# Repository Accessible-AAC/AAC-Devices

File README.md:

# AAC-Devices

Augmentative and alternative communications device design files based on inexpensive and open source technologies.

Printed circuit boards were designed using KiCAD (https://www.kicad.org/)

Enclosures were designed using OpenSCAD version 2015.03-2 (https://www.openscad.org/).

Solutions are designed around commodity electronic devices that should be inexpensive and readily available on-line.

<br />
This work is licensed under a <a rel="license" href="http://creativecommons.org/licenses/by-sa/4.0/">
Creative Commons Attribution-ShareAlike 4.0 International License</a>.

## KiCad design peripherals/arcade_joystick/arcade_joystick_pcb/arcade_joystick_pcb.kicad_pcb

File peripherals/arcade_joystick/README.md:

# Arcade Joystick

These directories contain design files for an arcade joystick peripheral.
 
This sensor can be plugged into an analog (yellow) controller input. It is activated by moving the handle.

## Assembly

Internal hardware mechanism is an arcade style 4/8 way joystick purchased from China.

It is held in place by four 8-32 x 1½" machine screws inserted into 4 embedded 8-32 nuts.

The joystick is connected to the interface PCB using hook-up wire:

    80 mm twisted pair soldered to D+, D-
    80 mm twisted pair soldered to R+, R-
    130 mm twisted pair soldered to L+, L-
    130 mm twisted pair soldered to U+, U-

## Handles

The threads on the joystick handle are compatible with an M6 nut.

<br />This work is licensed under a <a rel="license" href="http://creativecommons.org/licenses/by-sa/4.0/">
Creative Commons Attribution-ShareAlike 4.0 International License</a>.

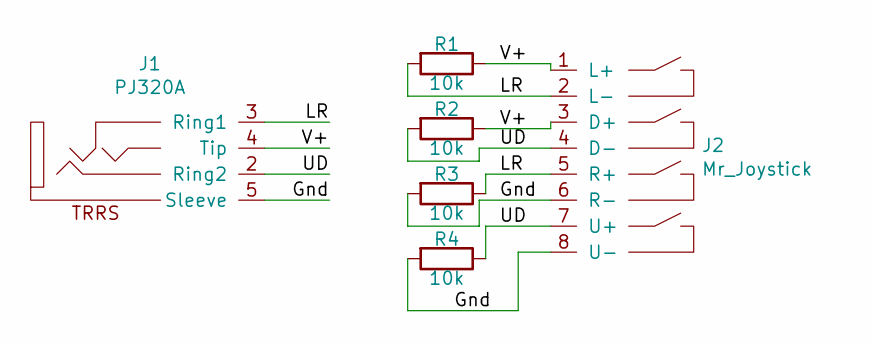
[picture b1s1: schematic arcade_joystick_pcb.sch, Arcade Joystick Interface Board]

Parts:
J1: PJ320A; PJ-320A
J2: Mr_Joystick
R1, R2, R3, R4: 10k; R_1206_3216Metric; LCSC C17902

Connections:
/Gnd: J1.5 (Sleeve), J2.6 (R-), J2.8 (U-), R3.2, R4.2
/LR: J1.3 (Ring1), J2.2 (L-), J2.5 (R+), R1.2, R3.1
/UD: J1.2 (Ring2), J2.4 (D-), J2.7 (U+), R2.2, R4.1
/V+: J1.4 (Tip), J2.1 (L+), J2.3 (D+), R1.1, R2.1

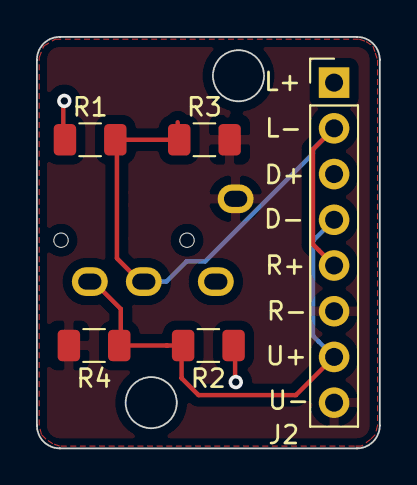
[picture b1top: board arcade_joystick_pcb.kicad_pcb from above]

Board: 2 copper layers, 19.1 x 22.9 mm, 6 parts (1 on the bottom side), 4 nets.

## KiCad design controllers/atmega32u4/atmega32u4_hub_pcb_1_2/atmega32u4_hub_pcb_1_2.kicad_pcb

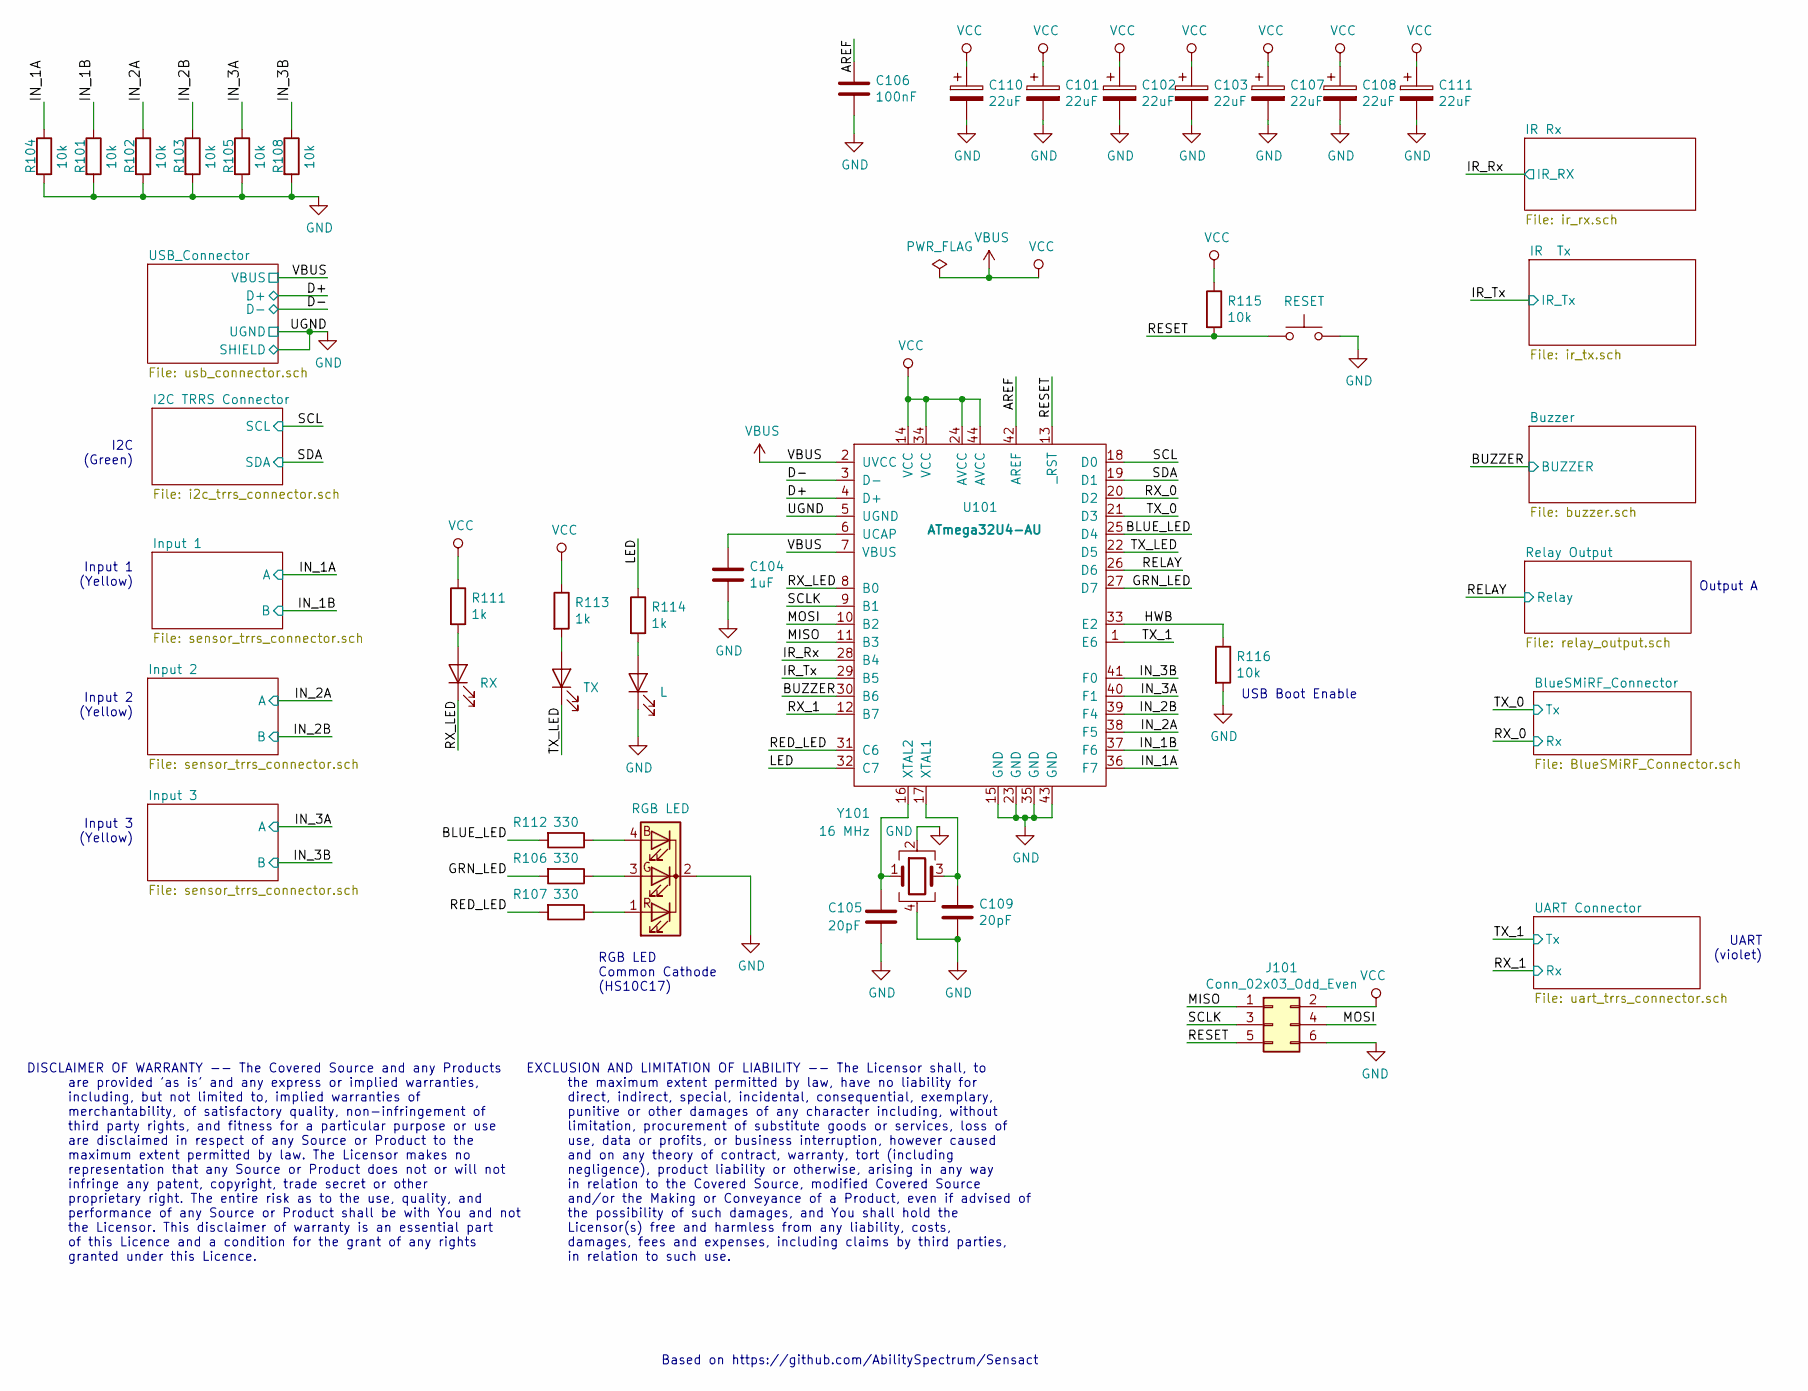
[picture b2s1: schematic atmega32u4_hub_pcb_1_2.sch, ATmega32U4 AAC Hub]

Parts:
C101, C102, C103, C107, C108, C110, C111: 22uF; C_0805_2012Metric; LCSC C45783
C104: 1uF; C_0805_2012Metric; LCSC C28323
C105, C109: 20pF; C_0603_1608Metric; LCSC C1648
C106: 100nF; C_0805_2012Metric; LCSC C49678
D101: RX; LED_0603_1608Metric; LCSC C72043
D102: RGB LED; LED_D5.0mm-4_RGB
D103: TX; LED_0603_1608Metric; LCSC C2286
D104: L; LED_0603_1608Metric; LCSC C72038
J101: Conn_02x03_Odd_Even; PinHeader_2x03_P2.54mm_Vertical
R101, R102, R103, R104, R105, R108, R115, R116: 10k; R_0603_1608Metric; LCSC C25804
R106, R107, R112: 330; R_0603_1608Metric; LCSC C23138
R111, R113, R114: 1k; R_0603_1608Metric; LCSC C21190
SW101: RESET; SW_PUSH_6mm
U101: ATmega32U4-AU; TQFP-44_10x10mm_P0.8mm; LCSC C44854
Y101: 16 MHz; Crystal_SMD_3225-4Pin_3.2x2.5mm; LCSC C13738

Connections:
/AREF: C106.1, U101.42 (AREF)
/BLUE_LED: R112.2, U101.25 (D4)
/BUZZER: U101.30 (B6); also elsewhere on the board
/D+: U101.4 (D+); also elsewhere on the board
/D-: U101.3 (D-); also elsewhere on the board
/GRN_LED: R106.2, U101.27 (D7)
/HWB: R116.1, U101.33 (E2)
/IN_3A: R105.1, U101.40 (F1); also elsewhere on the board
/IN_3B: R108.1, U101.41 (F0); also elsewhere on the board
/IR_Rx: U101.28 (B4); also elsewhere on the board
/IR_Tx: U101.29 (B5); also elsewhere on the board
/LED: R114.1, U101.32 (C7)
/MISO: J101.1, U101.11 (B3)
/MOSI: J101.4, U101.10 (B2)
/RED_LED: R107.2, U101.31 (C6)
/RELAY: U101.26 (D6); also elsewhere on the board
/RESET: J101.5, R115.2, SW101.1, U101.13 (_RST)
/RX_0: U101.20 (D2); also elsewhere on the board
/RX_1: U101.12 (B7); also elsewhere on the board
/RX_LED: D101.1 (K), U101.8 (B0)
/SCL: U101.18 (D0); also elsewhere on the board
/SCLK: J101.3, U101.9 (B1)
/SDA: U101.19 (D1); also elsewhere on the board
/TX_0: U101.21 (D3); also elsewhere on the board
/TX_1: U101.1 (E6); also elsewhere on the board
/TX_LED: D103.1 (K), U101.22 (D5)
GND: C101.2, C102.2, C103.2, C104.2, C105.2, C106.2, C107.2, C108.2, C109.2, C110.2, C111.2, D102.2 (K), D104.1 (K), J101.6, R101.2, R102.2, R103.2, R104.2, R105.2, R108.2, R116.2, SW101.2, U101.5 (UGND), U101.15 (GND), U101.23 (GND), U101.35 (GND), U101.43 (GND), Y101.2, Y101.4; also elsewhere on the board
unnamed: C104.1, U101.6 (UCAP)
unnamed: C105.1, U101.16 (XTAL2), Y101.1
unnamed: C109.1, U101.17 (XTAL1), Y101.3
unnamed: D101.2 (A), R111.2
unnamed: D102.1 (RA), R107.1
unnamed: D102.3 (GA), R106.1
unnamed: D102.4 (BA), R112.1
unnamed: D103.2 (A), R113.2
unnamed: D104.2 (A), R114.2
VBUS: C101.1, C102.1, C103.1, C107.1, C108.1, C110.1, C111.1, J101.2, R111.1, R113.1, R115.1, U101.2 (UVCC), U101.7 (VBUS), U101.14 (VCC), U101.24 (AVCC), U101.34 (VCC), U101.44 (AVCC); also elsewhere on the board

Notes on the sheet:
Input 1 (Yellow)
I2C (Green)
Input 2 (Yellow)
Input 3 (Yellow)
Output A
USB Boot Enable
RGB LED Common Cathode (HS10C17)
Based on https://github.com/AbilitySpectrum/Sensact
UART (violet)
DISCLAIMER OF WARRANTY -- The Covered Source and any Products are provided 'as is' and any express or implied warranties, including, but not limited to, implied warranties of merchantability, of satisfactory quality, non-infringement of third party rights, and fitness for a particular purpose or us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
EXCLUSION AND LIMITATION OF LIABILITY -- The Licensor shall, to the maximum extent permitted by law, have no liability for direct, indirect, special, incidental, consequential, exemplary, punitive or other damages of any character including, without limitation, procurement of substitute goods or se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

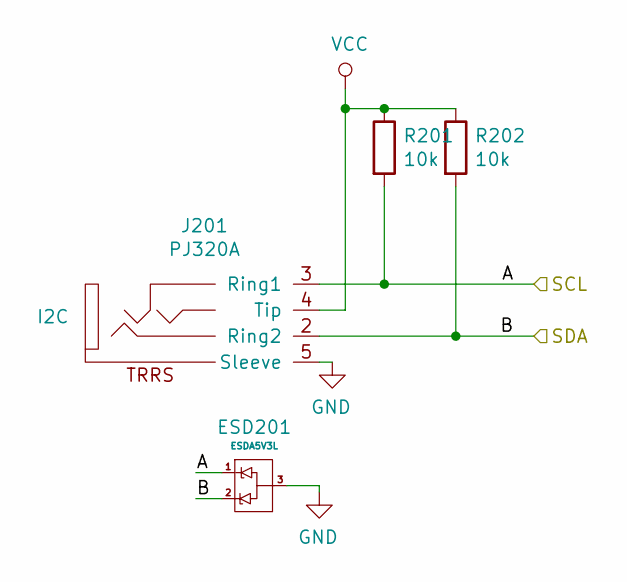
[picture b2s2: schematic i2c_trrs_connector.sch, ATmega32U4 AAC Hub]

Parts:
ESD201: ESDA5V3L; SOT-23; LCSC C87911
J201: PJ320A; PJ-320A
R201, R202: 10k; R_0603_1608Metric; LCSC C25804

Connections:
/SCL: ESD201.1, J201.3 (Ring1), R201.2; also elsewhere on the board
/SDA: ESD201.2, J201.2 (Ring2), R202.2; also elsewhere on the board
GND: ESD201.3, J201.5 (Sleeve); also elsewhere on the board
VBUS: J201.4 (Tip), R201.1, R202.1; also elsewhere on the board

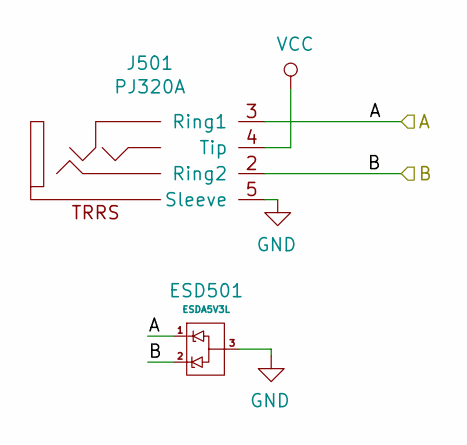
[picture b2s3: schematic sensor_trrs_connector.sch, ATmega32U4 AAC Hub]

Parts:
ESD401: ESDA5V3L; SOT-23; LCSC C87911
J301: PJ320A; PJ-320A

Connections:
GND: ESD401.3, J301.5 (Sleeve); also elsewhere on the board
VBUS: J301.4 (Tip); also elsewhere on the board

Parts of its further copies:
ESD301, ESD501: ESDA5V3L; SOT-23; LCSC C87911
J401, J501: PJ320A; PJ-320A

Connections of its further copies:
/IN_3A: ESD501.1, J501.3 (Ring1); also elsewhere on the board
/IN_3B: ESD501.2, J501.2 (Ring2); also elsewhere on the board
GND: ESD301.3, ESD501.3, J401.5 (Sleeve), J501.5 (Sleeve); also elsewhere on the board
VBUS: J401.4 (Tip), J501.4 (Tip); also elsewhere on the board

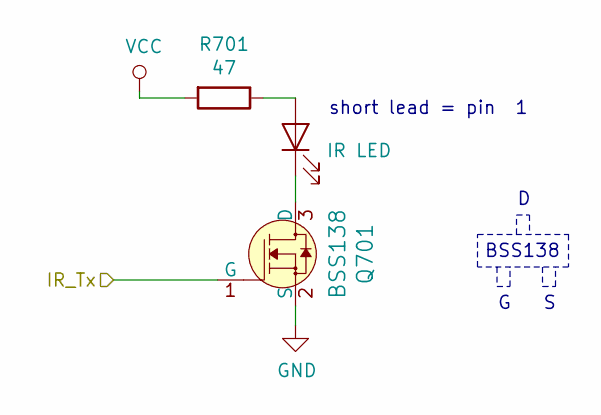
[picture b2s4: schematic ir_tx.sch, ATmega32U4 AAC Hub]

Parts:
D701: IR LED; LED_D5.0mm
Q701: BSS138; SOT-23; MPN BSS138; Digi-Key_PN BSS138CT-ND
R701: 47; R_1206_3216Metric; Part Number 1206W4J0470T5E; LCSC C25384

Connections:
/IR_Tx: Q701.1 (G); also elsewhere on the board
GND: Q701.2 (S); also elsewhere on the board
unnamed: D701.1 (K), Q701.3 (D)
unnamed: D701.2 (A), R701.1
VBUS: R701.2; also elsewhere on the board

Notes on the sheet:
BSS138
short lead = pin 1

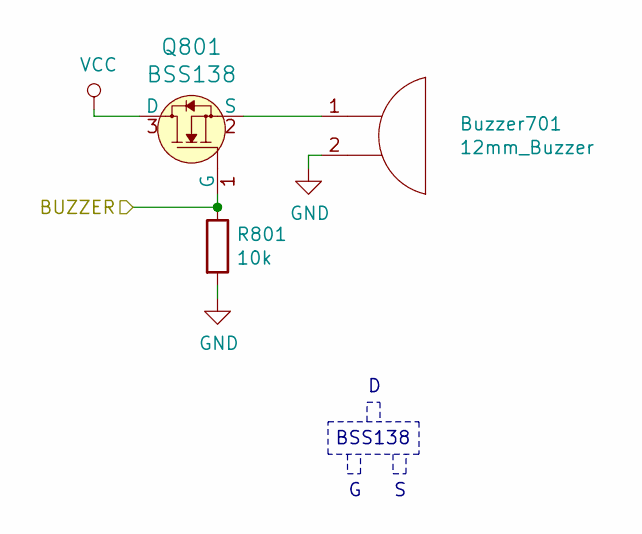
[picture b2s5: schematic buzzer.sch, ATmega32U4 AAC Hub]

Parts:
Buzzer701: 12mm_Buzzer; 12mm_buzzer
Q801: BSS138; SOT-23; MPN BSS138; Digi-Key_PN BSS138CT-ND
R801: 10k; R_0603_1608Metric; LCSC C25804

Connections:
/BUZZER: Q801.1 (G), R801.1; also elsewhere on the board
GND: Buzzer701.2, R801.2; also elsewhere on the board
unnamed: Buzzer701.1, Q801.2 (S)
VBUS: Q801.3 (D); also elsewhere on the board

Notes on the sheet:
BSS138

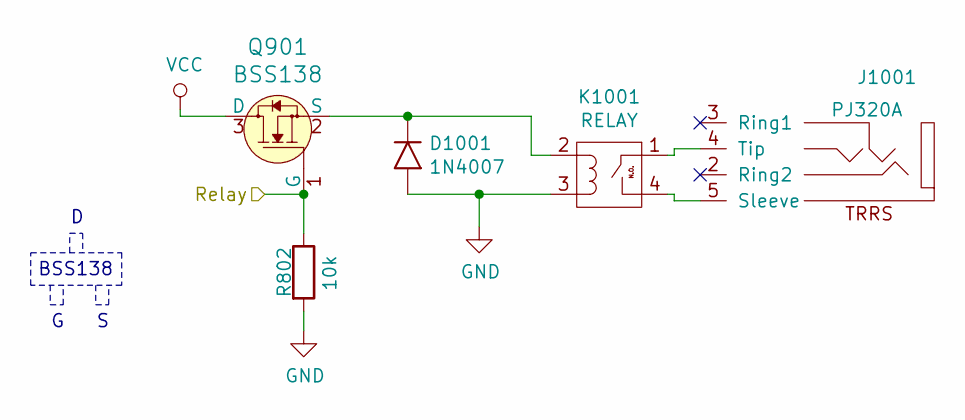
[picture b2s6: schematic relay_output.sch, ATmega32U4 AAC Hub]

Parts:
D901: 1N4007; D_SMA; LCSC C95872
J901: PJ320A; PJ-320A
K901: RELAY; sip-1a05
Q802: BSS138; SOT-23; MPN BSS138; Digi-Key_PN BSS138CT-ND
R802: 10k; R_0603_1608Metric; LCSC C25804

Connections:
/RELAY: R802.1; also elsewhere on the board
GND: R802.2; also elsewhere on the board

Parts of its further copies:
D1001: 1N4007; D_SMA; LCSC C95872
J1001: PJ320A; PJ-320A
K1001: RELAY; sip-1a05
Q901: BSS138; SOT-23; MPN BSS138; Digi-Key_PN BSS138CT-ND

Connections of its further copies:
/RELAY: Q901.1 (G); also elsewhere on the board
GND: D1001.2 (A), K1001.3; also elsewhere on the board
unnamed: D1001.1 (K), K1001.2, Q901.2 (S)
unnamed: J1001.4 (Tip), K1001.1
unnamed: J1001.5 (Sleeve), K1001.4
VBUS: Q901.3 (D); also elsewhere on the board

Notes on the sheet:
BSS138

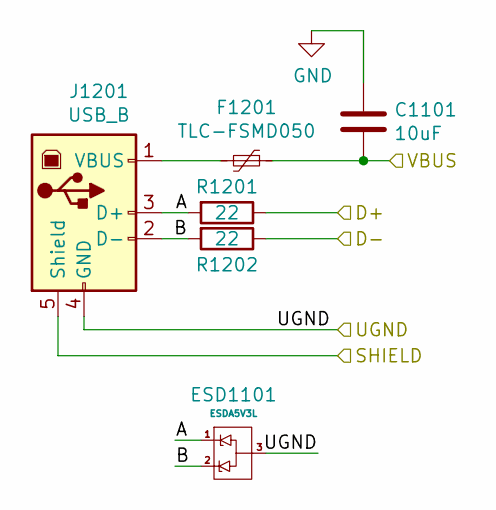
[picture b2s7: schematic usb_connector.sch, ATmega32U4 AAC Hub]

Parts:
C1101: 10uF; C_0805_2012Metric; LCSC C15850
ESD1101: ESDA5V3L; SOT-23; LCSC C87911
F1201: TLC-FSMD050; Fuse_0603_1608Metric; LCSC C261937
J1201: USB_B; USB_B_OST_USB-B1HSxx_Horizontal
R1201, R1202: 22; R_0603_1608Metric; LCSC C23345

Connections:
/D+: R1201.1; also elsewhere on the board
/D-: R1202.1; also elsewhere on the board
/USB_Connector/A: ESD1101.1, J1201.3 (D+), R1201.2
/USB_Connector/B: ESD1101.2, J1201.2 (D-), R1202.2
GND: C1101.1, ESD1101.3, J1201.4 (GND), J1201.5 (Shield); also elsewhere on the board
unnamed: F1201.2, J1201.1 (VBUS)
VBUS: C1101.2, F1201.1; also elsewhere on the board

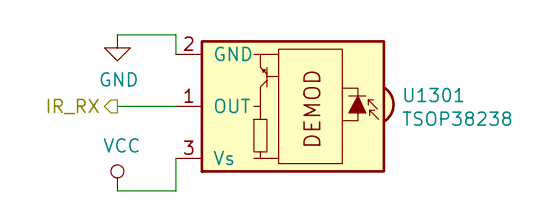
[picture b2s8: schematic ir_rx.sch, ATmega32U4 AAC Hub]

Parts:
U1301: TSOP38238; Vishay_MOLD-3Pin

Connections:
/IR_Rx: U1301.1 (OUT); also elsewhere on the board
GND: U1301.2 (GND); also elsewhere on the board
VBUS: U1301.3 (Vs); also elsewhere on the board

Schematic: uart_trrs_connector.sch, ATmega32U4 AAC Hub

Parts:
ESD1001: ESDA5V3L; SOT-23; LCSC C87911
J1101: PJ320A; PJ-320A

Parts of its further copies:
ESD1201: ESDA5V3L; SOT-23; LCSC C87911
J1202: PJ320A; PJ-320A

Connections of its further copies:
/RX_1: ESD1201.2, J1202.2 (Ring2); also elsewhere on the board
/TX_1: ESD1201.1, J1202.3 (Ring1); also elsewhere on the board
GND: ESD1201.3, J1202.5 (Sleeve); also elsewhere on the board
VBUS: J1202.4 (Tip); also elsewhere on the board

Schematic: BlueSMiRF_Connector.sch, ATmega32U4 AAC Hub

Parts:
ESD1202: ESDA5V3L; SOT-23; LCSC C87911
J1203: BlueSMiRF; BlueSMiRF_Socket

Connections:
/RX_0: ESD1202.2, J1203.3; also elsewhere on the board
/TX_0: ESD1202.1, J1203.2; also elsewhere on the board
GND: ESD1202.3, J1203.4; also elsewhere on the board
VBUS: J1203.5; also elsewhere on the board

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
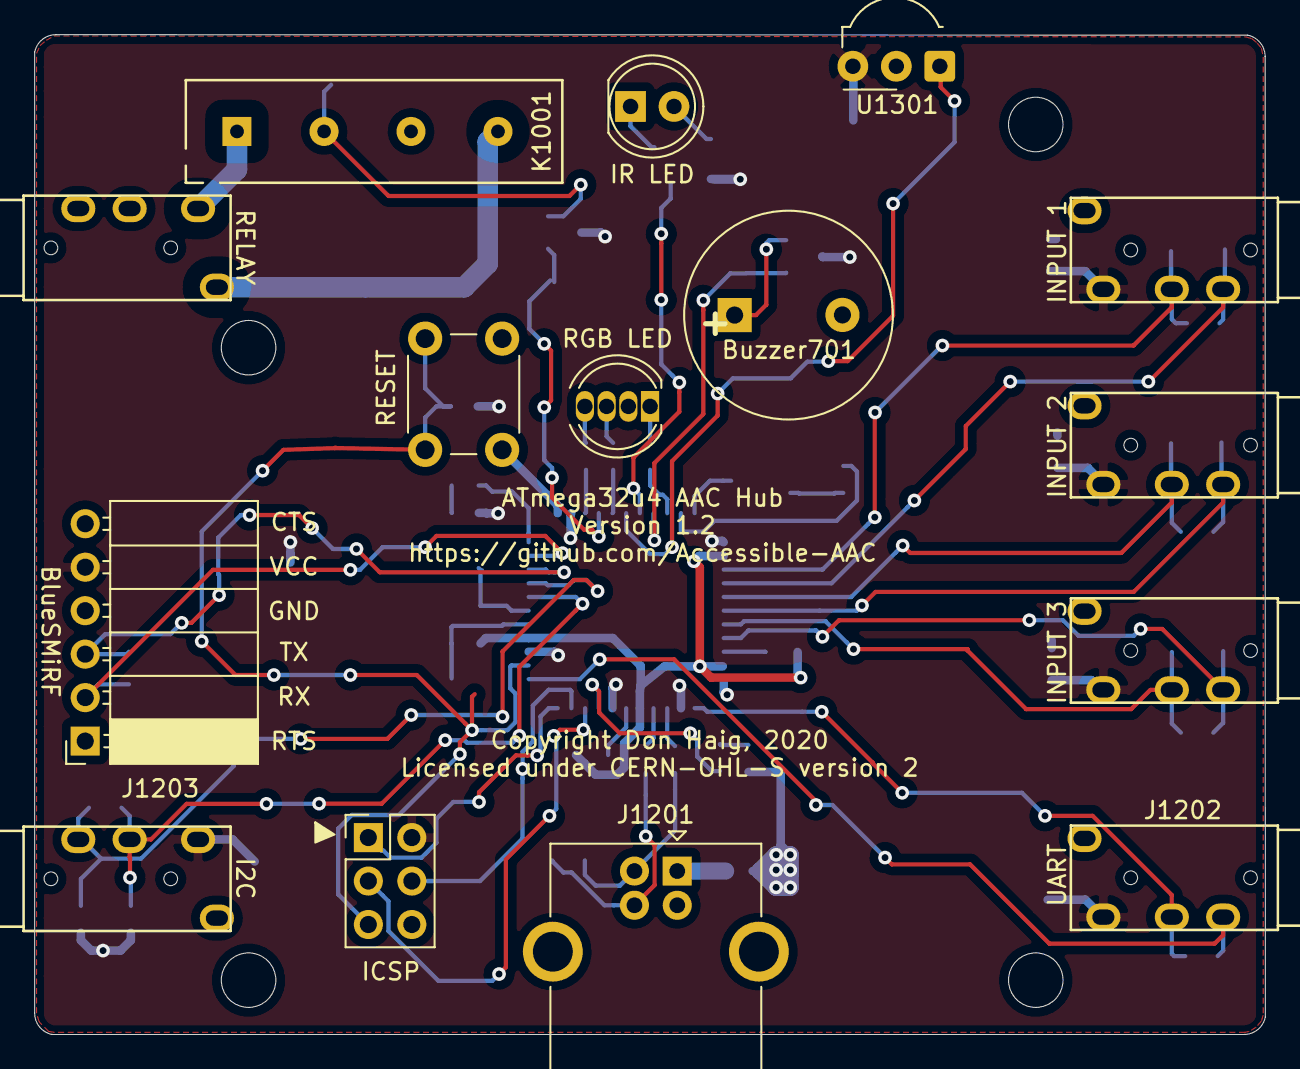
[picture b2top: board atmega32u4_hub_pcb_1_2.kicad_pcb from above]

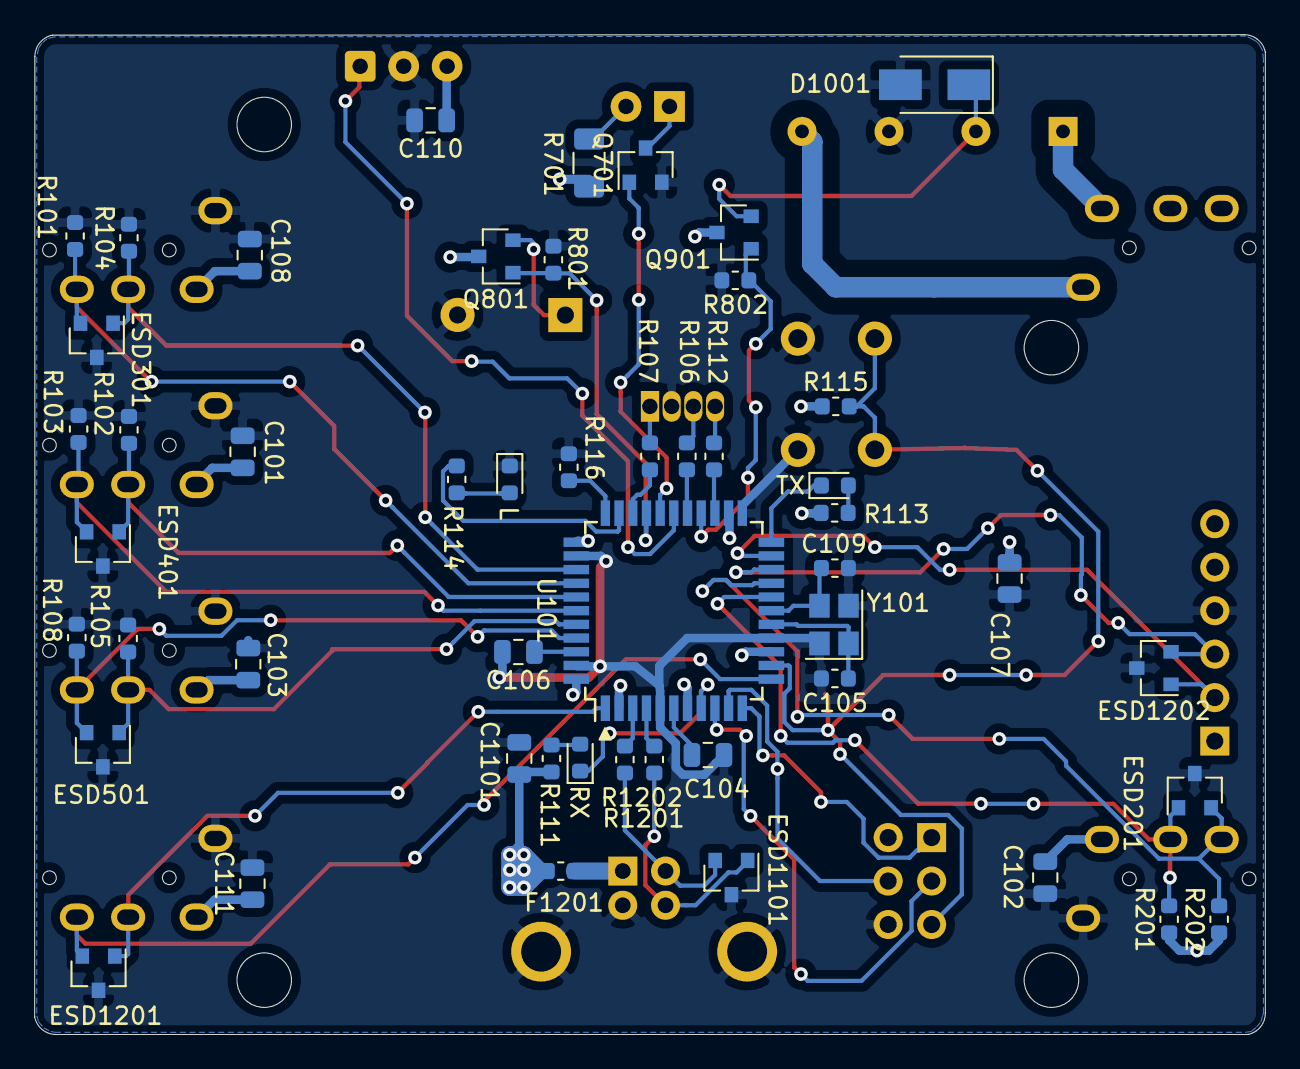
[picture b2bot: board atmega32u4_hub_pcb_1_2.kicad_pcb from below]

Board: 2 copper layers, 71.9 x 58.4 mm, 65 parts (50 on the bottom side), 50 nets.

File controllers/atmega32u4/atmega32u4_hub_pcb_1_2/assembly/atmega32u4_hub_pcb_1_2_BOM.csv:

Comment,Designator,Footprint, LCSC,
12mm_Buzzer,Buzzer701,,,https://www.aliexpress.com/item/4000133619336.html?spm=a2g0s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
22uF,"C101,C102,C103,C107,C108,C110,C111",805,C45783,https://lcsc.com/product-detail/Multilayer-Ceramic-Capacitor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
1uF,C104,805,C28323,https://lcsc.com/product-detail/Multilayer-Ceramic-Capacitor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
20pF,"C105,C109",603,C1648,https://lcsc.com/product-detail/Multilayer-Ceramic-Capacitor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
100nF,C106,805,C49678,https://lcsc.com/product-detail/Multilayer-Ceramic-Capacitor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
10uF,C1101,805,C15850,https://lcsc.com/product-detail/Multilayer-Ceramic-Capacitor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
1N4007,D1001,"SMA,DO-214AC",C95872,https://lcsc.com/product-detail/Diodes-General-Purpose_MDD-M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
RX,D101,603,C72043,https://lcsc.com/product-detail/Light-Emitting-Diodes-LED_Ev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
RGB LED,D102,,,https://www.aliexpress.com/item/1656753326.html?spm=a2g0s.90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
TX,D103,603,C72044,https://lcsc.com/product-detail/Light-Emitting-Diodes-LED_06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
L,D104,603,C72038,https://lcsc.com/product-detail/Light-Emitting-Diodes-LED_Ev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
IR LED,D701,,,
ESDA5V3L,"ESD201,ESD301,ESD401,ESD501,ESD1101,ESD1201,ESD1202",SOT-23-3, C87911,https://lcsc.com/product-detail/TVS_STMicroelectronics-ESDA5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
TLC-FSMD050,F1201,603,C261937,https://lcsc.com/product-detail/PTC-Resettable-Fuses_TLC-Ele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
Conn_02x03_Odd_Even,J101,PinHeader_2x03_P2.54mm_Vertical,C225518,https://lcsc.com/product-detail/Pin-Header-Female-Header_CJT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
USB_B,J1201,,C498173,https://lcsc.com/product-detail/New-Arrivals_SOFNG-USB-B01_C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
BlueSMiRF,J1203,, C225514,https://lcsc.com/product-detail/Pin-Header-Female-Header_CJT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
PJ320A,"J201,J301,J401,J501,J1001,J1202",,,https://www.aliexpress.com/item/32775943831.html?spm=a2g0s.9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
RELAY,K1001,,C10496,https://lcsc.com/product-detail/Relays_PAN-CHANG-SIP-1A05_C1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
BSS138,"Q701,Q801,Q901",SOT-23-3, C82045,https://lcsc.com/product-detail/MOSFET_ON-Semiconductor-BSS1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
10k,"R104,R101,R102,R103,R105,R108,R115,R116,R201,R202,R801,R802",603, C25804,https://lcsc.com/product-detail/Chip-Resistor-Surface-Mount_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
1k,"R111,R113,R114",603,C21190,https://lcsc.com/product-detail/Chip-Resistor-Surface-Mount_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
330,"R112,R106,R107",603,C23138,https://lcsc.com/product-detail/Chip-Resistor-Surface-Mount_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
22,"R1202,R1201",603,C23345,https://lcsc.com/product-detail/Chip-Resistor-Surface-Mount_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
47,R701,1206,  C25384,https://lcsc.com/product-detail/Chip-Resistor-Surface-Mount_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
RESET,SW101,6mm x 6mm, C455095,https://lcsc.com/product-detail/Tactile-Switches_XUNPU-TS-10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
ATmega32U4-AU,U101,QFP-44_10.0x10.0x0.8P,C44854,https://lcsc.com/product-detail/ATMEL-AVR_ATMEL_ATMEGA32U4-A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
TSOP38238,U1301,,,
16 MHz,Y101,SMD-3225_4P, C13738,https://lcsc.com/product-detail/SMD-Crystal-Resonators_Yangx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

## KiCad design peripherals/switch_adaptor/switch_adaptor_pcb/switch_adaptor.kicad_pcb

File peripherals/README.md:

# AAC Peripherals

These directories contain design files for various AAC peripherals.

The bases of the peripherals are colour coded according to the controller input that they should be plugged into:

Yellow : Analog (yellow) inputs

Green : I2C (green) inputs

<br />This work is licensed under a <a rel="license" href="http://creativecommons.org/licenses/by-sa/4.0/">
Creative Commons Attribution-ShareAlike 4.0 International License</a>.

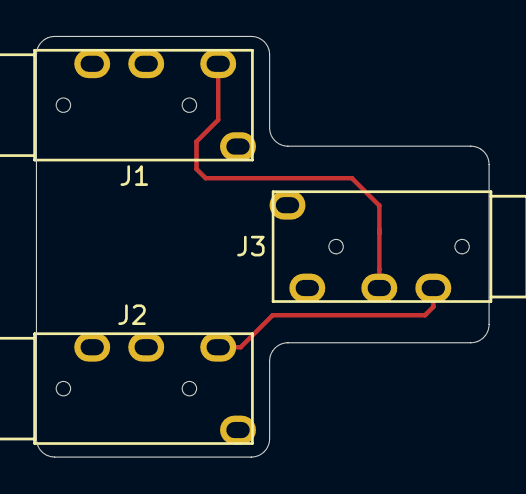
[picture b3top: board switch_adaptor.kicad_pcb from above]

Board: 2 copper layers, 25.1 x 23.4 mm, 3 parts (0 on the bottom side), 3 nets.

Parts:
J1, J2, J3: PJ320A; PJ-320A

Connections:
/SW1: J1.4, J3.3
/SW2: J2.4, J3.2
/Vcc: J1.2, J1.3, J1.5, J2.2, J2.3, J2.5, J3.4

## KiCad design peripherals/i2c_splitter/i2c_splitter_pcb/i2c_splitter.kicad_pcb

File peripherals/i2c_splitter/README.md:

# I2C Splitter

These directories contain design files for an i2c bus splitter, for use with an i2c (green) controller input.

This splitter can be used to connect two i2c (green base) peripherals to the same i2c (green) input port.

(Multiple splitters can be daisy-chained together to accommodate more i2c peripherals, subject to i2c bus limitation
with respect to peripheral addressing.)

## Assembly                                                                                                                                       

<br />This work is licensed under a <a rel="license" href="http://creativecommons.org/licenses/by-sa/4.0/">
Creative Commons Attribution-ShareAlike 4.0 International License</a>.

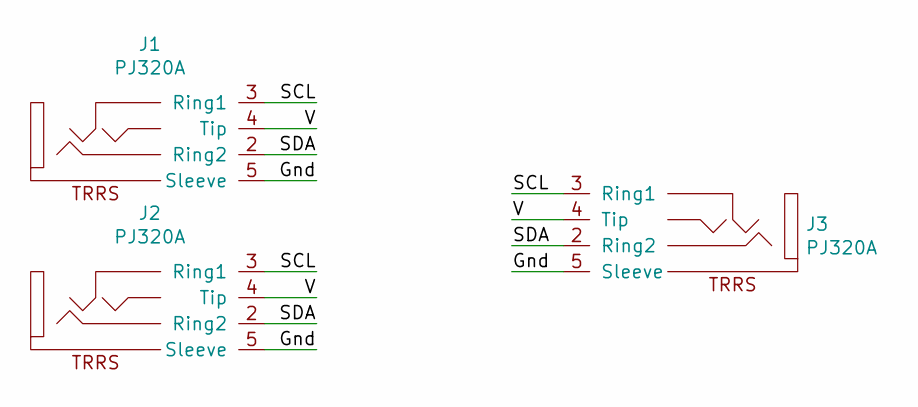
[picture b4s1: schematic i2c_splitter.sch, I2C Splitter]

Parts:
J1, J2, J3: PJ320A; PJ-320A

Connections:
/Gnd: J1.5 (Sleeve), J2.5 (Sleeve), J3.5 (Sleeve)
/SCL: J1.3 (Ring1), J2.3 (Ring1), J3.3 (Ring1)
/SDA: J1.2 (Ring2), J2.2 (Ring2), J3.2 (Ring2)
/V: J1.4 (Tip), J2.4 (Tip), J3.4 (Tip)

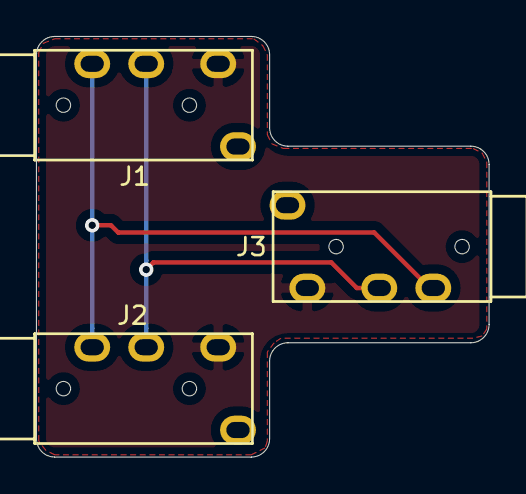
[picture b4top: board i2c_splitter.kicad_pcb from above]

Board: 2 copper layers, 25.1 x 23.4 mm, 3 parts (0 on the bottom side), 4 nets.

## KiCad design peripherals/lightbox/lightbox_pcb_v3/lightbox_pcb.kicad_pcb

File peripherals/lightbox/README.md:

# Lightbox Display

These directories contain design files for a lightbox display peripheral, for use with an i2c (green) controller input.

## Hardware

The lightbox is based on a Microchip MCP23008 8-Bit I/O Expander: <a rel="datasheet" 
href="https://ww1.microchip.com/downloads/en/DeviceDoc/21919e.pdf">Datasheet</a>

I2C Address: 0x20

## Assembly

<br />This work is licensed under a <a rel="license" href="http://creativecommons.org/licenses/by-sa/4.0/">
Creative Commons Attribution-ShareAlike 4.0 International License</a>.

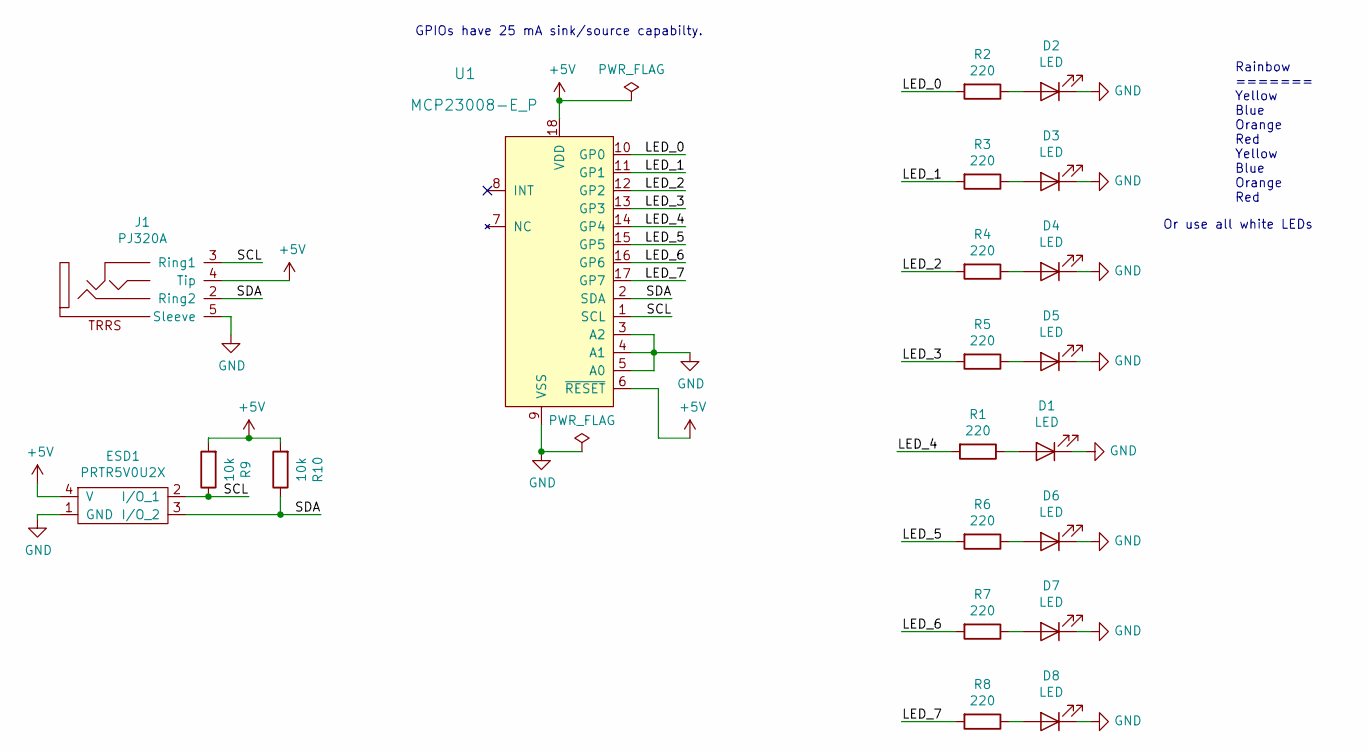
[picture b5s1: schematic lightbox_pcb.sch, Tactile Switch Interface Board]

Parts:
D1, D2, D3, D4, D5, D6, D7, D8: LED; LED_D3.0mm
ESD1: PRTR5V0U2X; SOT-143
J1: PJ320A; PJ-320A
R1, R2, R3, R4, R5, R6, R7, R8: 220; R_Axial_DIN0207_L6.3mm_D2.5mm_P7.62mm_Horizontal
R9, R10: 10k; R_Axial_DIN0207_L6.3mm_D2.5mm_P7.62mm_Horizontal
U1: MCP23008-E_P; DIP-18_W7.62mm; MPN MCP23008-E/P; Digi-Key_PN MCP23008-E/P-ND

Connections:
+5V: ESD1.4 (V), J1.4 (Tip), R9.2, R10.2, U1.6 (~RESET), U1.18 (VDD)
/LED_0: R2.2, U1.10 (GP0)
/LED_1: R3.2, U1.11 (GP1)
/LED_2: R4.2, U1.12 (GP2)
/LED_3: R5.2, U1.13 (GP3)
/LED_4: R1.2, U1.14 (GP4)
/LED_5: R6.2, U1.15 (GP5)
/LED_6: R7.2, U1.16 (GP6)
/LED_7: R8.2, U1.17 (GP7)
/SCL: ESD1.2 (I/O_1), J1.3 (Ring1), R9.1, U1.1 (SCL)
/SDA: ESD1.3 (I/O_2), J1.2 (Ring2), R10.1, U1.2 (SDA)
GND: D1.1 (K), D2.1 (K), D3.1 (K), D4.1 (K), D5.1 (K), D6.1 (K), D7.1 (K), D8.1 (K), ESD1.1 (GND), J1.5 (Sleeve), U1.3 (A2), U1.4 (A1), U1.5 (A0), U1.9 (VSS)
unnamed: D1.2 (A), R1.1
unnamed: D2.2 (A), R2.1
unnamed: D3.2 (A), R3.1
unnamed: D4.2 (A), R4.1
unnamed: D5.2 (A), R5.1
unnamed: D6.2 (A), R6.1
unnamed: D7.2 (A), R7.1
unnamed: D8.2 (A), R8.1

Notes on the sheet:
GPIOs have 25 mA sink/source capabilty.
Rainbow ======= Yellow Blue Orange Red Yellow Blue Orange Red
Or use all white LEDs

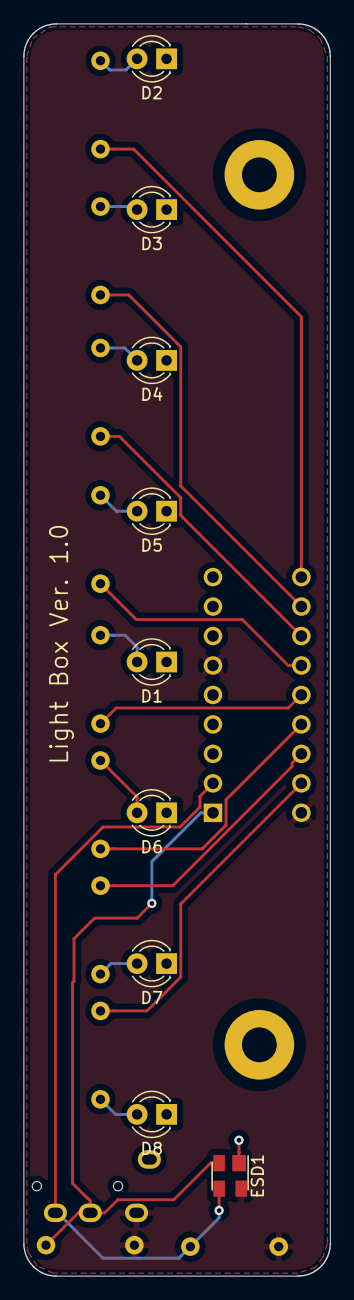
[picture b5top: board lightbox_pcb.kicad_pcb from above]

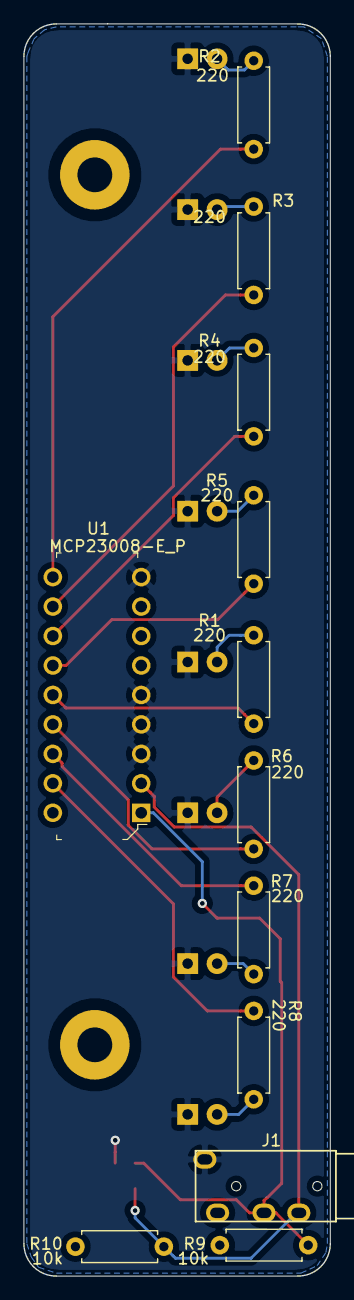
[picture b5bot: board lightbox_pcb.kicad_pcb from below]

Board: 2 copper layers, 26.4 x 108.0 mm, 23 parts (12 on the bottom side), 20 nets.

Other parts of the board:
1pin_prototyping, 1pin_prototyping#2: val**; 1pin_prototyping

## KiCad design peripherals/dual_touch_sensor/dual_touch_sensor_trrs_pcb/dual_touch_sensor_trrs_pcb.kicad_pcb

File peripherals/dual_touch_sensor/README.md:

# Dual Catalex Touch Sensor

These directories contain design files for a dual catalex touch sensor peripheral.

This sensor can be plugged into an analog (yellow) controller input. It is activated by touching the top, where indicated.

## Assembly

Catalex touch sensors should be tested before assembly to ensure that they will function correctly through the enclosure.

<br />This work is licensed under a <a rel="license" href="http://creativecommons.org/licenses/by-sa/4.0/">
Creative Commons Attribution-ShareAlike 4.0 International License</a>.

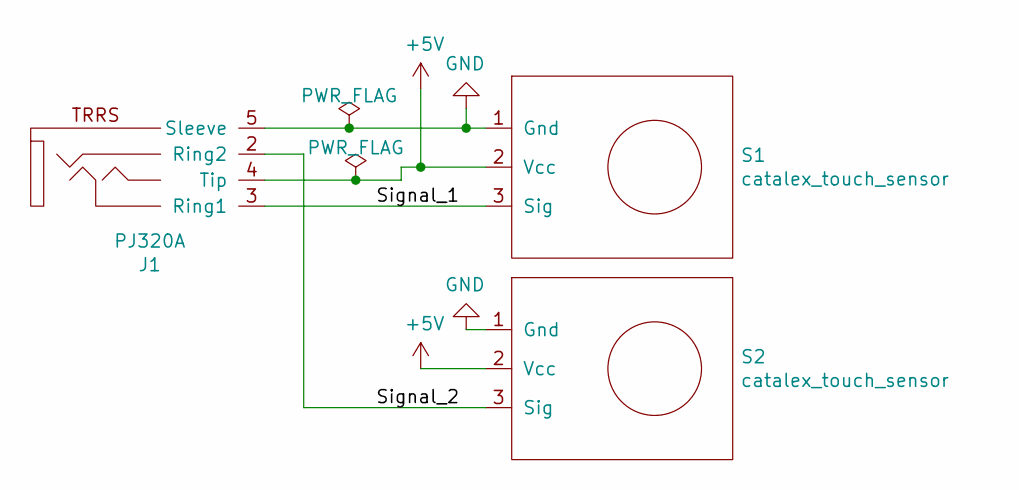
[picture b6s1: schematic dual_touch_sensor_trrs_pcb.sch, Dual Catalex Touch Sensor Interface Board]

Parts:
J1: PJ320A; PJ-320A
S1, S2: catalex_touch_sensor; Catalex_Touch_Module

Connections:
+5V: J1.4 (Tip), S1.2 (Vcc), S2.2 (Vcc)
/Signal_1: J1.3 (Ring1), S1.3 (Sig)
/Signal_2: J1.2 (Ring2), S2.3 (Sig)
GND: J1.5 (Sleeve), S1.1 (Gnd), S2.1 (Gnd)

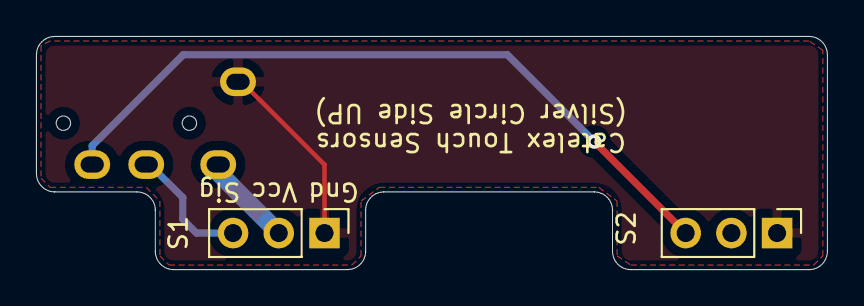
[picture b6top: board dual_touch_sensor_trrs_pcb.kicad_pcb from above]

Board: 2 copper layers, 43.9 x 13.0 mm, 3 parts (1 on the bottom side), 4 nets.

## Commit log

2019-11-26 Arduino Leonardo Controller Enclosure Design Files
2019-11-30 Peripheral Design Files
2019-11-30 fixed typo
2020-02-11 Updated README.md for tactile switch design.
2020-02-21 Extension rod for HW-504 joytick
2020-02-21 Cleaned up code
2020-03-18 Updated arcade joystick pcb design
2020-03-18 Updated switch adaptor design
2020-07-12 Increased tactile switch PCB hole diameters - increased hole diameters to 1.2mm to accommodate pins on 12mm x 12mm tactile switches.
2020-07-12 Updated tactile switch README file
2020-09-16 Refactored palm rest design
2020-11-06 Added missing openscad straight header model
2020-11-14 tactile_switch_pcb_v2 gerbers zipped for manufacture
2021-11-09 Update README.md
    https://forum.kicad.info/t/warning-avoid-all-links-to-kicad-pcb-org-use-kicad-org/31521
2021-12-17 AtMega32U04 controller designs added
2021-12-17 Update CERN OHL files

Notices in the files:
README.md:
<img alt="Creative Commons License"
style="border-width:0" src="https://i.creativecommons.org/l/by-sa/4.0/88x31.png" />
controllers/atmega32u4/atmega32u4_hub_pcb_1_2/BlueSMiRF_Connector.sch:
(c) Copyright 2020, Don Haig
Licensed under CERN-OHL-S V 2
controllers/atmega32u4/atmega32u4_hub_pcb_1_2/atmega32u4_hub_pcb_1_2.kicad_pcb:
Licensed under CERN-OHL-S version 2
Copyright Don Haig, 2020
controllers/atmega32u4/atmega32u4_hub_pcb_1_2/atmega32u4_hub_pcb_1_2.sch:
granted under this Licence.
peripherals/README.md:
CC BY-SA 4.0
